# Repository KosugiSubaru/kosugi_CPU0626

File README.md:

# kosugi_CPU0626

自作16bit ISA・CPUコアと、対応するCコンパイラ・アセンブラ、周辺HWドライバ一式。

## システム接続関係

Cプログラム(オセロ)をコンパイラでバイナリに変換し、命令メモリ経由でCPUに供給する。CPUはデータメモリを介してVRAM・キーボードドライバとやり取りし、HDMIドライバでディスプレイに出力する。赤枠が本リポジトリで自作した部分(コンパイラ、Cプログラム、CPU、キーボードドライバ、キーボード)。

##　CPUスペック

| 項目 | 値 |
|---|---|
| 実体 | TangNano9K (FPGA) に書き込み |
| 動作周波数 | 可変 |
| 命令数 | 16 |
| 命令セット | 手動定義 |
| Verilog回路 | Gemini 3 Flash で自動生成 |
| データ幅 | 16bit |
| レジスタ数 | 16 |
| 命令語長 | 16bit |
| ゼロレジスタ | R0 |

## 構成

- `ISA_definition.yaml` — 命令セット定義(命令一覧・ビットフィールド・フラグ仕様)
- `CPU/` — CPUコア(Verilog RTL)、Verilatorシミュレーション・論理合成スクリプト
- `COMPILER/` — Cコンパイラ(`compiler/`)とアセンブラ(`assembler/`)、テストプログラム(`programs/`)
- `HW_DRIVER/` — HDMI出力・マトリクスキーボード等のFPGA周辺ドライバ(Verilog)
- `KiCad/` — 基板(キーボード)のKiCadプロジェクト

## ISA

16bit固定長、ALU系・即値系・メモリアクセス系・分岐/ジャンプ系の命令を定義(詳細は [ISA_definition.yaml](ISA_definition.yaml))。

## データメモリマップ

| アドレス(Decimal) | 内容 |
|---|---|
| 0〜2399 | VRAM |
| 2400〜3429 | Global(グローバル変数) |
| 3430〜4453 | Stack |
| 4454 | Embedded LEDs |
| 4455 | External LEDs |
| 4456～4457 | Keyboard |

データメモリ(0〜)はVRAM・グローバル変数領域・スタックの後ろに、LEDやキーボード入出力用のメモリマップドI/Oを配置している。

## 実装メモ

- Cコンパイラ: [9cc](https://github.com/rui314/9cc) を参考に自作。フロントエンドはLL(1)構文解析、バックエンドはスタックマシン向けコード生成。
- アセンブラ: Claude Codeで作成。長距離ジャンプは `auipc` + `asi` + `addi` に変換してアドレス16bitを充填する。

### 規模感

- Cコンパイラ本体: 約560行(C言語)
  - `stdio.h` などの標準ライブラリはinclude不可。入出力関数は自作(`printf`/`scanf`等は使用不可)
  - 宣言できる型は `int` のみ(すべて16bit確保)。構造体・2次元配列は未対応
- 生成アセンブリ: 約16200行(スタックマシン向け・最適化なしのコンパイラのため冗長だが、ちゃんと動作する)
- 生成バイナリ: 16bit × 16245命令 = 32490byte ≈ 32KB

## シミュレーション

### Cプログラムをコンパイル→アセンブルし、CPUの命令メモリに書き込む

```sh
cd COMPILER
./test.sh
```

`programs/myothello.c` をコンパイル・アセンブルし、`CPU/rtl/memory/imem/machine_code_bin.dat` に機械語を書き込みます。

### CPUをシミュレーション

```sh
cd CPU/script
./build_verilator.sh
```

Verilatorでビルドし、`tb_top_gen.cpp` によるテストベンチを実行します(波形: `tb_top_gen.vcd`)。

### 論理合成・回路図生成

```sh
cd CPU/script
./synthesize.sh
```

`rtl/cpu/` 配下の各モジュールをyosysで論理合成し、netlistsvgで回路図(SVG)を生成します。

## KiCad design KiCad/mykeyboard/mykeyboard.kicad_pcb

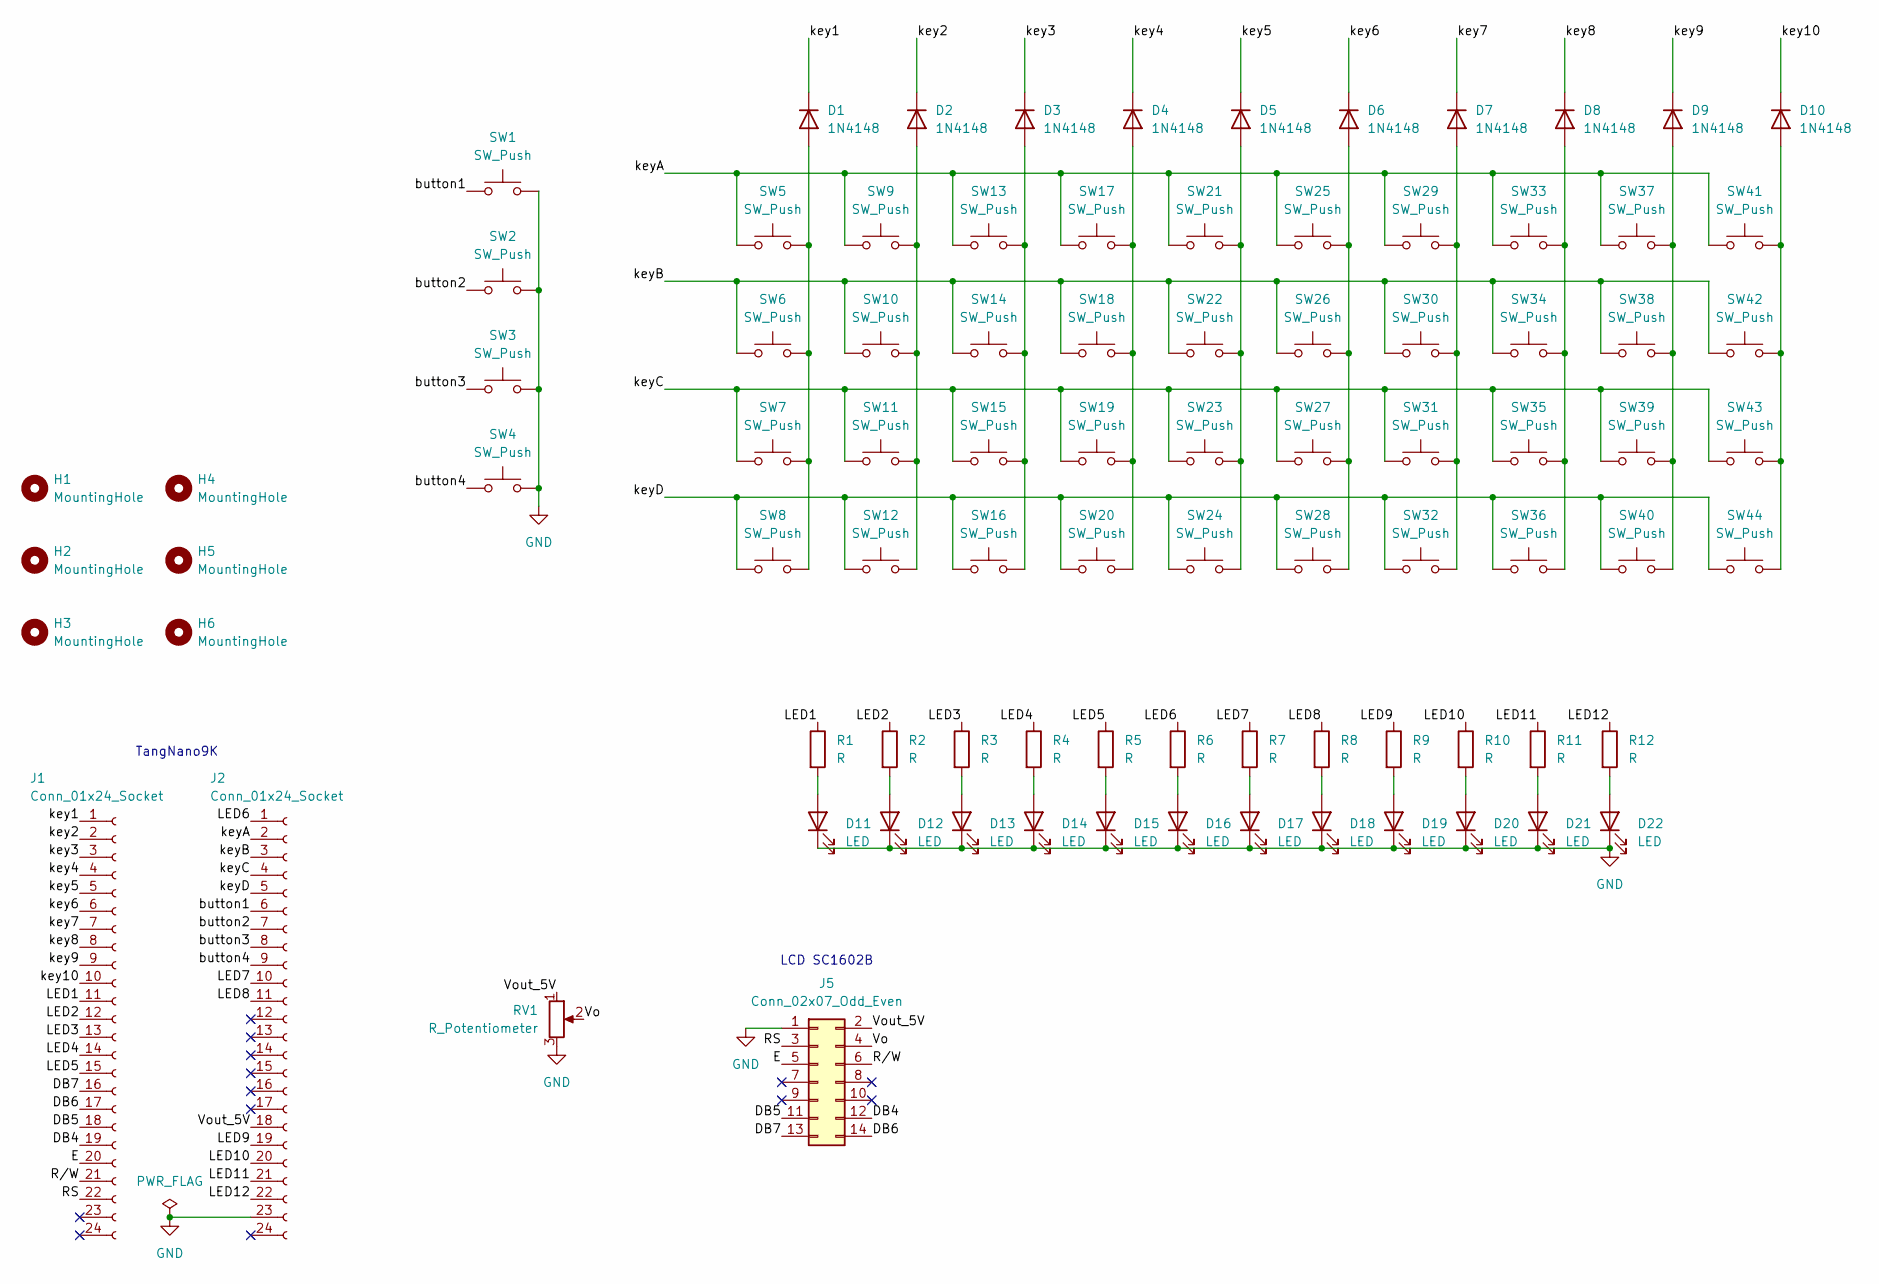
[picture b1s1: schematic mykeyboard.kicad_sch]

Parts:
D1, D2, D3, D4, D5, D6, D7, D8, D9, D10: 1N4148; D_DO-35_SOD27_P7.62mm_Horizontal
D11, D12, D13, D14, D15, D16, D17, D18, D19, D20, D21, D22: LED; LED_D3.0mm
H1, H2, H3, H4, H5, H6: MountingHole; MountingHole_3.2mm_M3
J1, J2: Conn_01x24_Socket; PinSocket_1x24_P2.54mm_Vertical
J5: Conn_02x07_Odd_Even; PinSocket_2x07_P2.54mm_Vertical
R1, R2, R3, R4, R5, R6, R7, R8, R9, R10, R11, R12: R; R_Axial_DIN0204_L3.6mm_D1.6mm_P7.62mm_Horizontal
RV1: R_Potentiometer; 3362P
SW1, SW2, SW3, SW4, SW5, SW6, SW7, SW8, SW9, SW10, SW11, SW12, SW13, SW14, SW15, SW16, SW17, SW18, SW19, SW20, SW21, SW22, SW23, SW24, SW25, SW26, SW27, SW28, SW29, SW30, SW31, SW32, SW33, SW34, SW35, SW36, SW37, SW38, SW39, SW40, SW41, SW42, SW43, SW44: SW_Push; SW_Cherry_MX_1.00u_PCB

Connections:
/DB4: J1.19, J5.12
/DB5: J1.18, J5.11
/DB6: J1.17, J5.14
/DB7: J1.16, J5.13
/E: J1.20, J5.5
/LED1: J1.11, R1.1
/LED2: J1.12, R2.1
/LED3: J1.13, R3.1
/LED4: J1.14, R4.1
/LED5: J1.15, R5.1
/LED6: J2.1, R6.1
/LED7: J2.10, R7.1
/LED8: J2.11, R8.1
/LED9: J2.19, R9.1
/LED10: J2.20, R10.1
/LED11: J2.21, R11.1
/LED12: J2.22, R12.1
/RS: J1.22, J5.3
/R/W: J1.21, J5.6
/Vo: J5.4, RV1.2
/Vout_5V: J2.18, J5.2, RV1.1
/button1: J2.6, SW1.1
/button2: J2.7, SW2.1
/button3: J2.8, SW3.1
/button4: J2.9, SW4.1
/key1: D1.1 (K), J1.1
/key2: D2.1 (K), J1.2
/key3: D3.1 (K), J1.3
/key4: D4.1 (K), J1.4
/key5: D5.1 (K), J1.5
/key6: D6.1 (K), J1.6
/key7: D7.1 (K), J1.7
/key8: D8.1 (K), J1.8
/key9: D9.1 (K), J1.9
/key10: D10.1 (K), J1.10
/keyA: J2.2, SW5.1, SW9.1, SW13.1, SW17.1, SW21.1, SW25.1, SW29.1, SW33.1, SW37.1, SW41.1
/keyB: J2.3, SW6.1, SW10.1, SW14.1, SW18.1, SW22.1, SW26.1, SW30.1, SW34.1, SW38.1, SW42.1
/keyC: J2.4, SW7.1, SW11.1, SW15.1, SW19.1, SW23.1, SW27.1, SW31.1, SW35.1, SW39.1, SW43.1
/keyD: J2.5, SW8.1, SW12.1, SW16.1, SW20.1, SW24.1, SW28.1, SW32.1, SW36.1, SW40.1, SW44.1
GND: D11.1 (K), D12.1 (K), D13.1 (K), D14.1 (K), D15.1 (K), D16.1 (K), D17.1 (K), D18.1 (K), D19.1 (K), D20.1 (K), D21.1 (K), D22.1 (K), J2.23, J5.1, RV1.3, SW1.2, SW2.2, SW3.2, SW4.2
unnamed: D1.2 (A), SW5.2, SW6.2, SW7.2, SW8.2
unnamed: D2.2 (A), SW9.2, SW10.2, SW11.2, SW12.2
unnamed: D3.2 (A), SW13.2, SW14.2, SW15.2, SW16.2
unnamed: D4.2 (A), SW17.2, SW18.2, SW19.2, SW20.2
unnamed: D5.2 (A), SW21.2, SW22.2, SW23.2, SW24.2
unnamed: D6.2 (A), SW25.2, SW26.2, SW27.2, SW28.2
unnamed: D7.2 (A), SW29.2, SW30.2, SW31.2, SW32.2
unnamed: D8.2 (A), SW33.2, SW34.2, SW35.2, SW36.2
unnamed: D9.2 (A), SW37.2, SW38.2, SW39.2, SW40.2
unnamed: D10.2 (A), SW41.2, SW42.2, SW43.2, SW44.2
unnamed: D11.2 (A), R1.2
unnamed: D12.2 (A), R2.2
unnamed: D13.2 (A), R3.2
unnamed: D14.2 (A), R4.2
unnamed: D15.2 (A), R5.2
unnamed: D16.2 (A), R6.2
unnamed: D17.2 (A), R7.2
unnamed: D18.2 (A), R8.2
unnamed: D19.2 (A), R9.2
unnamed: D20.2 (A), R10.2
unnamed: D21.2 (A), R11.2
unnamed: D22.2 (A), R12.2

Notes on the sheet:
LCD SC1602B
TangNano9K

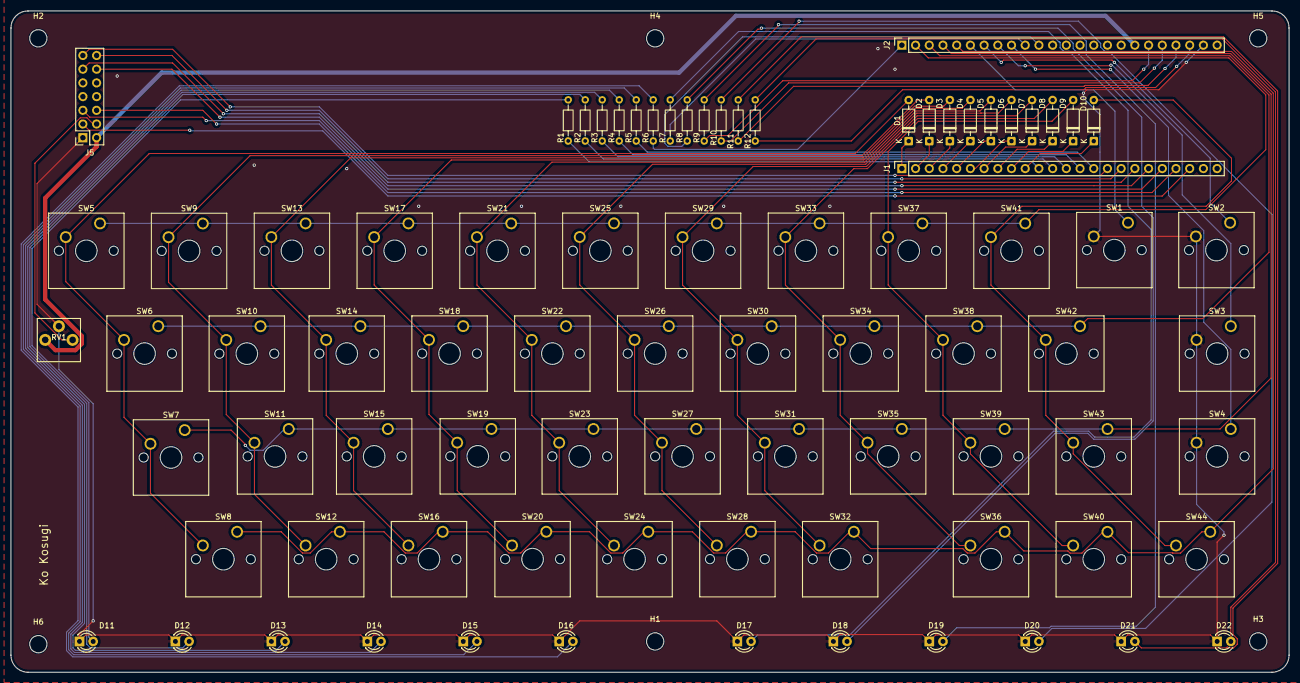
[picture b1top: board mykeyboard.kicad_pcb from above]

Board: 2 copper layers, 236.9 x 122.6 mm, 88 parts (0 on the bottom side), 62 nets.

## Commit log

2026-06-26 260626
2026-06-26 add dmem_table
2026-06-26 modify
